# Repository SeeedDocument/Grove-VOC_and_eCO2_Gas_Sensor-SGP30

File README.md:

# Grove-VOC_and_eCO2_Gas_Sensor-SGP30

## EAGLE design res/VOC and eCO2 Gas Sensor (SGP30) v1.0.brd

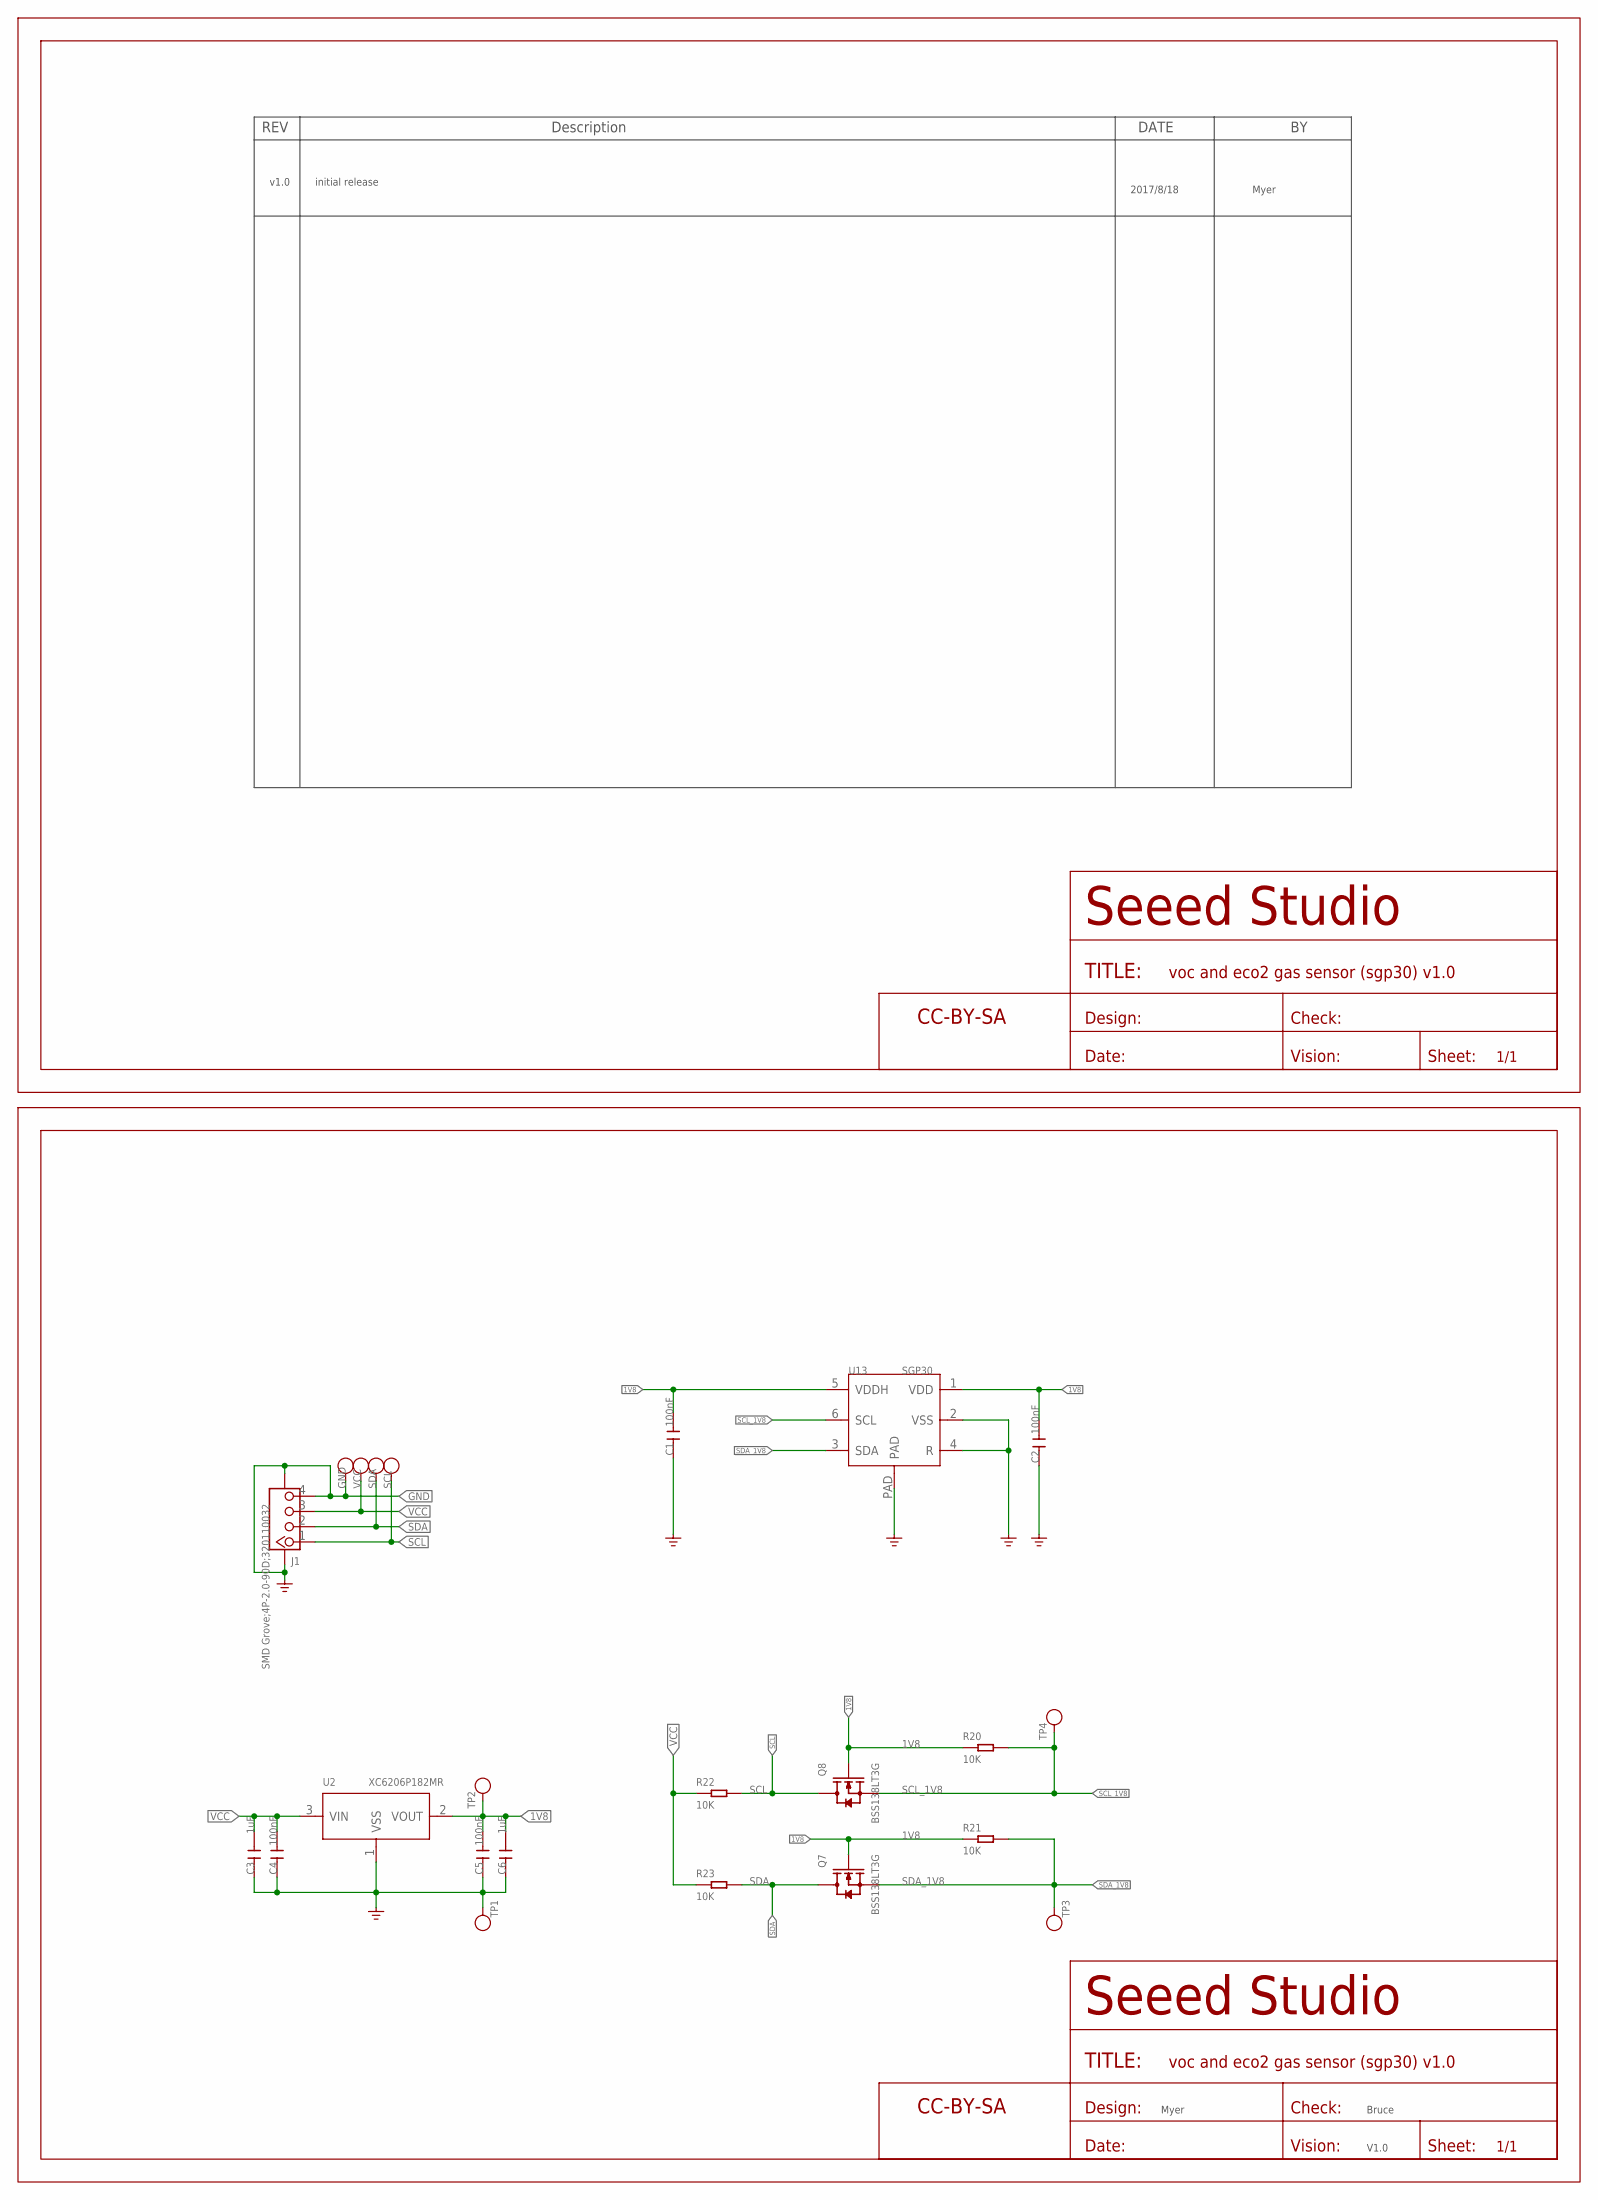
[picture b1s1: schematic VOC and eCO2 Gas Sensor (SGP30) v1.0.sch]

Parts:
C1, C2, C4, C5: 100nF; C0603
C3, C6: 1uF; C0603
FR1, FR2: SEEEDSTUDIO-OPEN-SCH-FRAME; SEEEDSTUDIO-PCB-FRAME
GND: TEST-POINT'4545'; TP-D45MIL
J1: SMD Grove;4P-2.0-90D;320110032; HW4-SMD-2.0-90D
Q7, Q8: BSS138LT3G; SOT-23
R20, R21, R22, R23: 10K; R0603
SCL: TEST-POINT'4545'; TP-D45MIL
SDA: TEST-POINT'4545'; TP-D45MIL
TP1, TP2, TP3, TP4: TEST-POINT'4545'; TP-D45MIL
U2: XC6206P182MR; SOT-23
U13: SGP30; DFN6-0.8-2.45X2.45X0.9MM
VCC: TEST-POINT'4545'; TP-D45MIL

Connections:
1V8: C1.1, C2.1, C5.1, C6.1, Q7.1 (G), Q8.1 (G), R20.1, R21.1, TP2.T, U2.2 (VOUT), U13.1 (VDD), U13.5 (VDDH)
GND: C1.2, C2.2, C3.2, C4.2, C5.2, C6.2, GND.T, J1.4, J1.SS1, J1.SS2, TP1.T, U2.1 (VSS), U13.2 (VSS), U13.4 (R), U13.PAD
SCL: J1.1, Q8.3 (D), R22.2, SCL.T
SCL_1V8: Q8.2 (S), R20.2, TP4.T, U13.6 (SCL)
SDA: J1.2, Q7.3 (D), R23.2, SDA.T
SDA_1V8: Q7.2 (S), R21.2, TP3.T, U13.3 (SDA)
VCC: C3.1, C4.1, J1.3, R22.1, R23.1, U2.3 (VIN), VCC.T

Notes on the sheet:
v1.0
initial release
2017/8/18
Myer
Bruce
V1.0

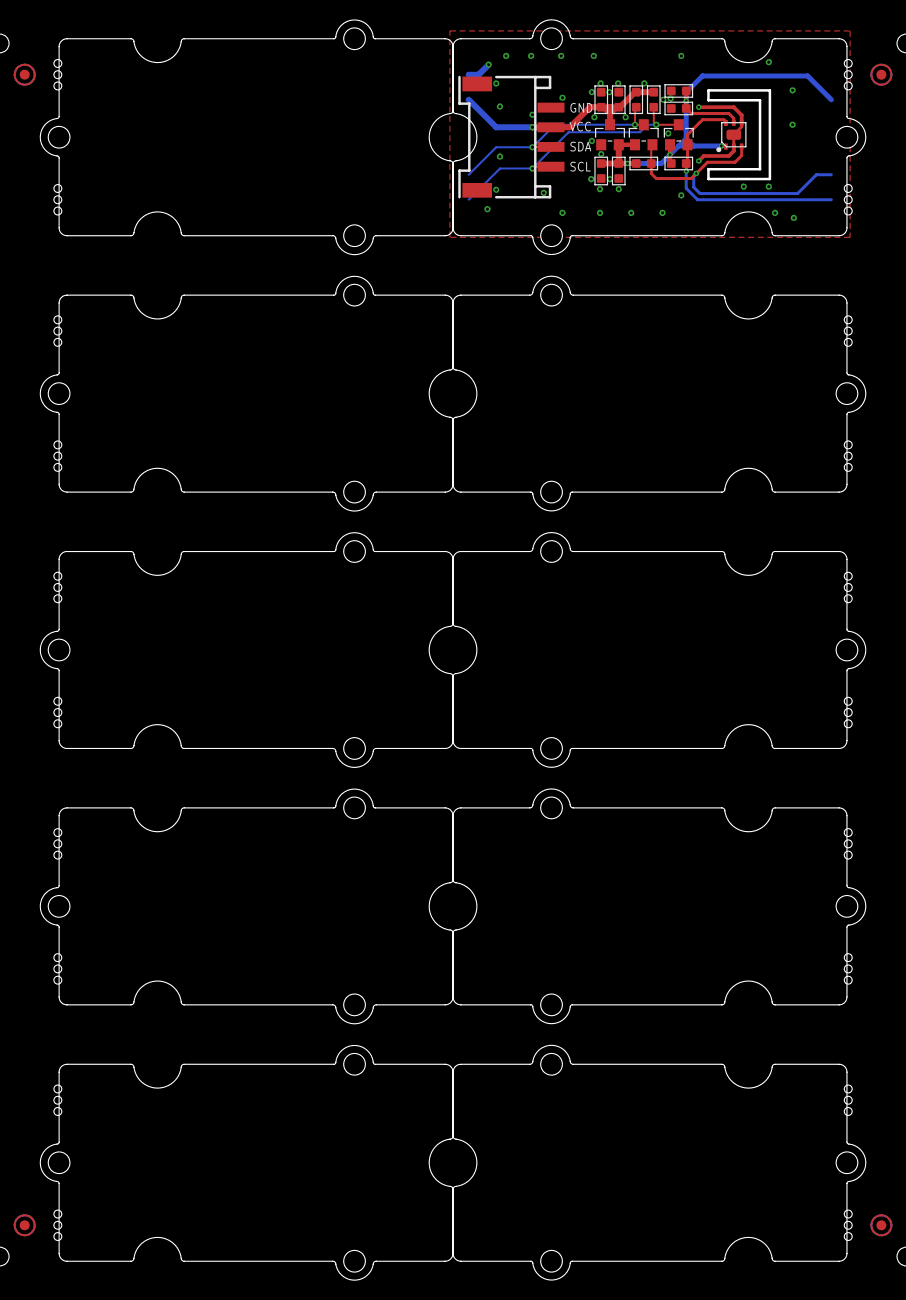
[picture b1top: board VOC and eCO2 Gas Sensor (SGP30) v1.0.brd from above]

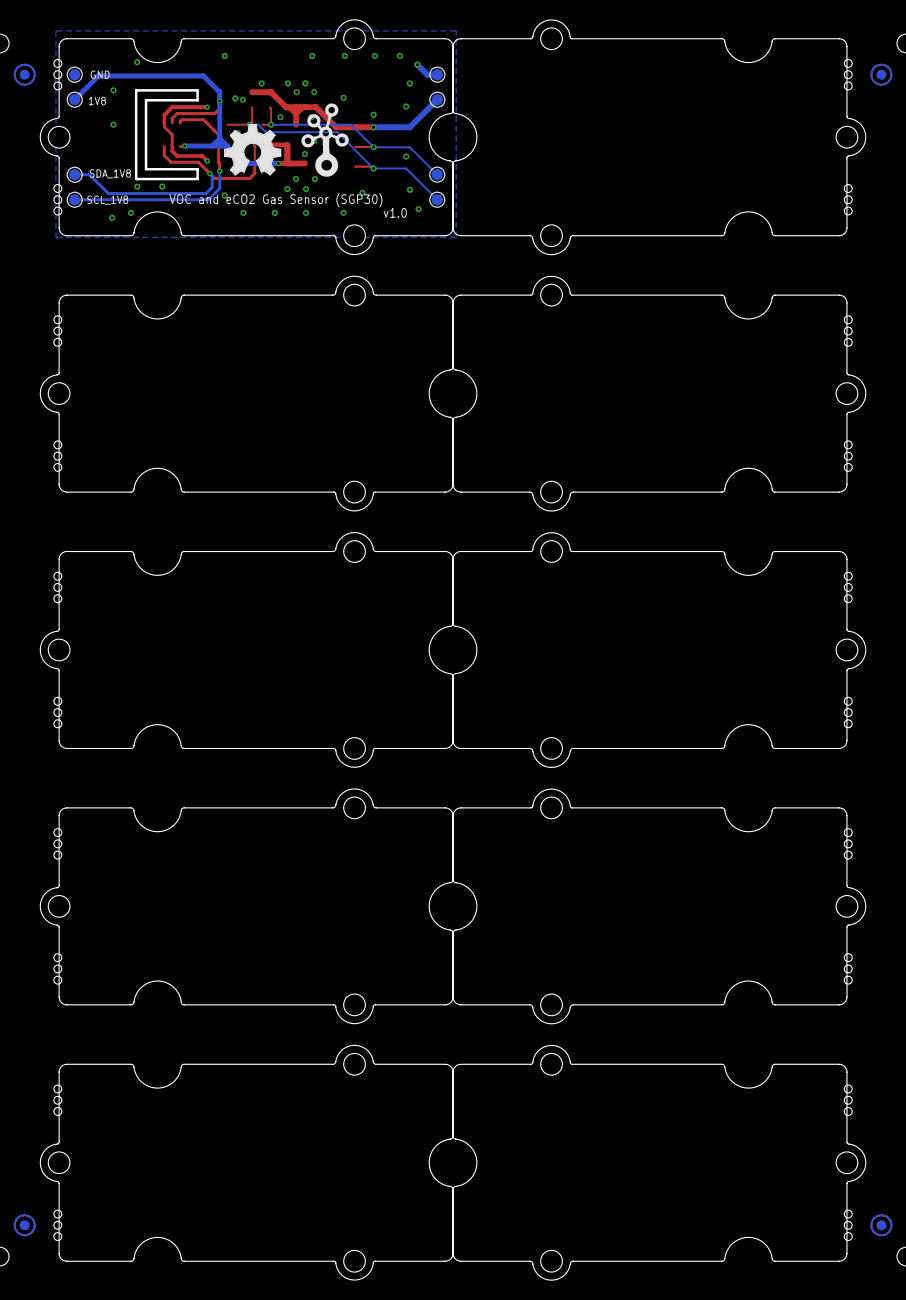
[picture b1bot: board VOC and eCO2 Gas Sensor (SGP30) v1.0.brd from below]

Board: 2 copper layers, 83.8 x 128.0 mm, 45 parts (14 on the bottom side), 7 nets.

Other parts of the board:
P1, P2, P3, P4, P5, P6, P7, P8: ROUND-MARK-1.0
U3, U4, U5, U6, U7, U8, U9, U10, U11, U12: GROVE-TEST-PLATFORM
U$3: OSHW_FILLX200_NOTEXT
U$4: TWIGLOGO

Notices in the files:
parts and their libraries:
moudle-new: This work is licensed under the Creative Commons Attribution 4.0 International License.
To view a copy of this license,visit:
http://creativecommons.org/licenses/by-sa/4.0
moudle-new: CC-BY-SA
